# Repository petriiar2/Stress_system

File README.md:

# Physiological Monitoring System - Hardware Design & Sensor Integration

> **PCC1 Project | KTH Royal Institute of Technology | MSc Medical Engineering | Stockholm, 2026**  
> *This repository covers only the hardware design, sensor selection, wiring, and embedded firmware — the physical core of the system.*
> *Other aspects of the project ( software component , website ) not considered in this repository*

---

## Table of Contents

1. [Project Overview](#1-project-overview)
2. [System Architecture](#2-system-architecture)
3. [Internal Station — Patient Side](#3-internal-station--patient-side)
4. [External Station — Dentist Side](#4-external-station--dentist-side)
5. [Sensor Reference](#5-sensor-reference)
   - [Pressure Sensor](#51-pressure-sensor--abpdrrv060mgaa5)
   - [GSR Sensor](#52-gsr-sensor--galvanic-skin-response)
   - [Moisture Sensor](#53-moisture-sensor--adafruit-stemma)
   - [PPG Sensor](#54-ppg-sensor--max30102)
6. [Microcontrollers & Communication](#6-microcontrollers--communication)
7. [Power Supply](#7-power-supply)
8. [PCB](#8-pcb--enclosure)
9. [Current Limitations & Future Work](#9-current-limitations--future-work)
10. [Authorship & Contributions](#10-authorship--contributions)

---

## 1. Project Overview

Dental patients cannot speak during procedures. The traditional workaround — raising a hand to signal pain — forces dentists to split their attention between precise work under magnifying loupes and watching for a hand signal outside their field of view. It is also binary: the signal says *stop*, but conveys nothing about intensity or rising discomfort.

**BM-Dentist** is a Bluetooth-enabled physiological monitoring system that gives patients a richer, low-effort communication channel while providing dentists with objective, real-time data about patient comfort:

- A **squeeze ball** lets the patient signal pain by squeezing harder or with squeeze patterns (1 squeeze = mild, 2 = moderate, 3+ = severe).
- **Involuntary physiological sensors** (GSR + skin moisture) detect stress independently of the patient's conscious action — catching anxiety before it reaches the threshold of deliberate signalling.
- **LED ring indicators** on the dentist's side are positioned within their natural visual field and communicate pain and stress levels through colour and intensity without requiring the dentist to look away.
- A **web dashboard** logs all signals in real time and generates post-procedure statistics for quality improvement.

The system is designed as a prototype towards clinical use — not yet a certified medical device.

---

## 2. System Architecture

The system consists of three interconnected subsystems:

```
┌──────────────────────────────┐        BLE 5.0         ┌──────────────────────────────────────┐
│     INTERNAL STATION         │ ────────────────────►  │         EXTERNAL STATION             │
│        (Patient Side)        │                        │          (Dentist Side)              │
│                              │                        │                                      │
│  Pressure Sensor             │                        │  nRF52840 #1  ──UART──  nRF52840 #2  │
│  GSR Sensor                  │  XIAO nRF52840         │  LED Pain Ring          OLED Display │
│  Moisture Sensor             │  (BLE Peripheral)      │  LED Stress Ring        Buttons      │
│  MAX30102 (PPG)              │                        │  (BLE Central)          (BLE→USB)    │
│                              │                        │                                      │
└──────────────────────────────┘                        └──────────────┬───────────────────────┘
                                                                       │ USB Serial
                                                              ┌────────▼────────┐
                                                              │   WEB APP       │
                                                              │  (HTML/JS)      │
                                                              │  Real-time plot │
                                                              │  Post-proc stats│
                                                              └─────────────────┘
```

**Data flow summary:**

1. Sensors → Internal XIAO nRF52840 via analog ADC / I²C
2. Internal nRF → External nRF #1 via BLE UART (20 Hz)
3. External nRF #1 → LED rings (pain & stress visualisation) + External nRF #2 via UART
4. External nRF #2 → Computer via USB Serial → Web app

The web/software layer (dashboard, statistical analysis, CSV export) was developed by other team members and is referenced here for context only.

---

## 3. Internal Station — Patient Side

The internal station is the patient-held device. It houses all sensors, the microcontroller, and the BLE radio inside a custom 3D-printed enclosure designed for comfortable grip. Sensors that must contact the patient's skin (electrodes, moisture pad) exit the enclosure via JST connectors and are attached externally.

<p align="center">
  
  &nbsp;
  
</p>

### What it does

- Reads all four sensors at **20 Hz** via a continuous polling loop
- Packages readings into a CSV string: `pressure,gsr,moisture\n`
- Transmits over **BLE UART** to the external station
- Performs **min-max normalisation** against individually calibrated baseline values
- Drives a **status LED** (pin D10) to confirm active transmission

### Calibration

Before a procedure, a 5-second calibration sequence is triggered from the dentist side:

| Phase | Patient action | What is recorded |
|-------|---------------|-----------------|
| Resting | Hold balloon without squeezing | `P_min` — baseline pressure |
| Max squeeze | Squeeze as hard as possible | `P_max` — individual squeeze ceiling |
| Resting (continuous) | Stay relaxed | `GSR_baseline` — calm-state conductance average |

Subsequent readings are normalised as:

```
pressure_norm = (P_current - P_min) / (P_max - P_min)
stress_norm   = |GSR_current - GSR_baseline| / GSR_range
```

Patient gender and age category are also collected at calibration time (they affect pain thresholds), though in the current prototype the demographic adjustment coefficients are set to neutral (A=1.0, B=0.0) pending clinical data.

---

## 4. External Station — Dentist Side

The dentist-side station receives data wirelessly and translates it into immediate visual feedback — no screen-watching required.

<p align="center">
  
  &nbsp;
  
</p>

### Dual-microcontroller architecture

Two XIAO nRF52840 boards are connected by a UART link (TX/RX crossed: D6↔D7):

**nRF52840 #1 — Signal processing & LED control**

- Acts as **BLE Central**: scans for and connects to the internal station (`"SensorNode"`)
- Parses the incoming CSV string and normalises sensor values
- Maps normalised pain to the number of illuminated LEDs on the **green pain ring**
- Maps normalised stress to the number of illuminated LEDs on the **blue stress ring**
- Flips stress ring colour to **red** when stress normalised value > 75% (urgent alert)
- Supports two pain-signalling modes (selectable at runtime):
  - **Direct mode**: squeeze force → proportional LED count
  - **Pattern mode**: counts squeeze edges in a sliding time window → 1 squeeze = few LEDs, 2 = moderate, 3+ = many
- Forwards raw data to nRF #2 via UART during working mode

**nRF52840 #2 — Interface & data relay**

- Drives the **OLED menu display** and three navigation buttons (Up / Down / Enter)
- Sends configuration commands to nRF #1:
  - `CALIB,<gender>,<age>` — start calibration
  - `RESET_CALIB` — wipe calibration
  - `WORKCFG` — start working mode with selected options
  - `WORK_END` — stop working mode, return to sleep
- Relays raw sensor data to the computer via BLE → USB Serial

### Operating modes

| Mode | Description |
|------|-------------|
| **Sleep** | BLE connection active, command exchange only — no data streaming or LED updates |
| **Working** | Full data streaming at 20 Hz, LED feedback active, data sent to computer |

---

## 5. Sensor Reference

### 5.1 Pressure Sensor — ABPDRRV060MGAA5

| Property | Value |
|----------|-------|
| Type | Analog MEMS pressure sensor |
| Interface | Analog voltage → ADC pin D2 |
| Supply | 3.3 V |
| ADC resolution | 12-bit (0–4095) |
| Physical connection | Flexible tubing → squeeze balloon (water bottle) |
| Sampling rate | 20 Hz |

**Purpose:** The primary intentional pain-signalling channel. The patient squeezes a balloon; the pressure sensor sits inside the enclosure connected by tubing, so there is no direct electronic contact with the patient's hand. This improves hygiene and allows the balloon to be replaced/sterilised between patients.

**What we get:** An analogue voltage proportional to balloon pressure. After calibration, this maps linearly to a 0–100% pain scale. In pattern mode, rising edges are counted over a sliding window to detect discrete squeeze events.

**Why this sensor:** The specific sensor was supplied to the team and is well-matched to the use case — it captures a deliberate, high signal-to-noise signal that requires no inference to interpret.

---

### 5.2 GSR Sensor — Galvanic Skin Response

| Property | Value |
|----------|-------|
| Type | Skin conductance, analog |
| Interface | Analog voltage → ADC pin D0 |
| Supply | 3.3 V |
| Electrode placement | Index finger + middle finger |
| Sampling rate | 20 Hz |

**Purpose:** Continuous, involuntary stress monitoring. Galvanic skin response measures changes in sweat gland activity driven by the sympathetic nervous system. It captures anticipatory anxiety — the patient may start showing stress before consciously deciding to squeeze.

**What we get:** A slow-varying analogue voltage that rises as skin conductance increases (higher stress → more perspiration → lower resistance → higher conductance). The deviation from the calibrated calm baseline is used as the stress metric.

**Why this sensor:** GSR is a well-established proxy for sympathetic arousal. Practical alternatives (e.g., dedicated EDA modules) had longer delivery times; the chosen module was available immediately and is straightforward to integrate with a single ADC pin.

**Wiring:** Two finger-clip electrodes connect to the sensor module via wires that exit the enclosure through a JST socket. The module output goes to pin D0.

---

### 5.3 Moisture Sensor — Adafruit STEMMA

| Property | Value |
|----------|-------|
| Type | Capacitive soil moisture sensor (repurposed) |
| Interface | Analog voltage → ADC pin D1 |
| Supply | 3.3 V |
| Placement | Palm contact (external, JST connector) |
| Sampling rate | 20 Hz |

**Purpose:** Secondary stress indicator via perspiration. Stress-induced sweating changes the dielectric properties of the skin surface, which the capacitive sensor detects as a change in output voltage.

**What we get:** An analogue voltage that varies with surface moisture. In our pilot validation, moisture features showed near-complete binary separation between no-stress and stress conditions (AUC ≈ 0.02–0.035, Cliff's δ ≈ −0.93 to −0.96 — moisture *decreases* in our sensor's output with higher sweat, reflecting sensor polarity).

**Important caveat:** This sensor is designed for soil, not human skin. Its readings are highly sensitive to contact area and the rigid structure makes consistent placement difficult. It is treated as an **exploratory channel** in the current prototype. A future iteration should replace it with a skin-validated conductance or hydration sensor.

**Wiring:** The sensor pad exits the enclosure via JST connector and is held against the patient's palm.

---

### 5.4 PPG Sensor — MAX30102

| Property | Value |
|----------|-------|
| Type | Photoplethysmographic (optical heart rate + SpO₂) |
| Interface | I²C → pins D4 (SDA) / D5 (SCL) |
| Supply | 3.3 V |
| Interrupt pin | D3 (INT, optional) |

**Purpose:** Heart rate and pulse-related metrics are strong indicators of physiological stress. HRV (heart rate variability) in particular is sensitive to autonomic nervous system state.

**Current status:** ⚠️ **Not used in the current validated prototype.** One of the two purchased modules was defective (internal short). The second produced unstable readings. The JST connector and I²C lines remain present on the PCB for future integration. Results in this report do not rely on PPG data.

**Why this sensor:** Selected primarily on cost, feature set, and community support under a limited budget. A future iteration should source a verified module or use an alternative such as the MAX86150.

---

## 6. Microcontrollers & Communication

### Seeed Studio XIAO nRF52840

Used for all three microcontroller roles (internal station + both external boards).

| Spec | Value |
|------|-------|
| CPU | ARM Cortex-M4 @ 64 MHz |
| BLE | 5.0 integrated |
| ADC | 12-bit, 6 analog pins |
| Size | 20 × 17.5 mm |
| Supply | 3.3 V logic; powered via VBUS (5 V) |
| I²C | Hardware I²C on D4/D5 |
| UART | Hardware Serial1 on D6/D7 |

### BLE Configuration

- Internal board advertises as peripheral under name `"SensorNode"`
- External board #1 acts as central, scans and connects to `"SensorNode"`
- BLE UART service emulates serial over Bluetooth
- Data transmitted at 20 Hz; format: `"pressure,gsr,moisture\n"`
- ADC resolution set explicitly: `analogReadResolution(12)`

### UART Between External Boards

- Pins: `D6(#1) → D7(#2)`, `D7(#1) → D6(#2)` (TX/RX crossed)
- Baud rate: **115200**
- Commands flow #2 → #1; raw data flows #1 → #2
- In sleep mode: command exchange only. In working mode: full 20 Hz data stream.

---

## 7. Power Supply

### MB102 Breadboard Power Module

Used on both internal and external stations.

| Output | Used for |
|--------|----------|
| 5 V | XIAO VBUS pin, LED rings (5 V NeoPixel-type) |
| 3.3 V | All sensors (pressure, GSR, moisture, PPG) |

- Each XIAO board provides its own 3.3 V rail from its onboard regulator — two separate 3.3 V rails on the external station to distribute load.
- All boards and sensors share a **common ground**.
- MB102 includes overcharge/overdischarge protection.

---

## 8. PCB 

### PCB Design

Schematics and PCB layouts were designed in **KiCad**. Key design decisions:

- **JST connectors** used extensively throughout — sensors on the internal board and interface elements on the external board are all physically external to the PCB, so connectors allow clean cable management and easy swapping.
- PCB fabrication within university facilities was not feasible in the project timeline, so components were soldered onto **prototyping (perfboard) boards** following the KiCad layout.

KiCad project files are included in `/internal/` or `/external/` .

---

## 9. Current Limitations & Future Work

| Area | Current state | Planned improvement |
|------|--------------|---------------------|
| PPG (heart rate) | Unstable — excluded from prototype | Source verified MAX30102 or MAX86150; repeat validation |
| Moisture sensor | Exploratory — not skin-specific | Replace with validated skin conductance/hydration sensor |
| Demographic calibration | Coefficients set to neutral (A=1, B=0) | Add clinically derived thresholds per gender/age group |
| Clinical validation | Simulated stress (video induction), 1 subject | Ethically approved trials with real dental patients |
| Enclosure | Internal box only printed | Print external box; ergonomic redesign for sterile grip |
| Accessibility | Hand squeeze only | Add foot-operated or capacitive-touch alternative inputs |
| Sterilisation | Not yet validated | Material selection and sterilisation protocol testing |

---

## 10. Authorship & Contributions

The hardware design presented in this repository — including sensor selection and wiring,
PCB schematics, microcontroller configuration, BLE/UART communication
architecture, and embedded firmware for data acquisition and LED control — was designed
and implemented by **Iaroslav Petrishchev**.

The following parts of the system are the work of other team members and are therefore
not covered in this repository:

- **Web application & real-time dashboard** (HTML/JS, Chart.js, Web Serial API) — *Naya Nasr & Yanzi Yu*
- **Post-procedure statistical analysis & CSV export** — *Naya Nasr & Yanzi Yu*
- **Clinical research, sensor rationale & validation study** — *Naya Nasr & Yanzi Yu*

> Full project report available upon request.

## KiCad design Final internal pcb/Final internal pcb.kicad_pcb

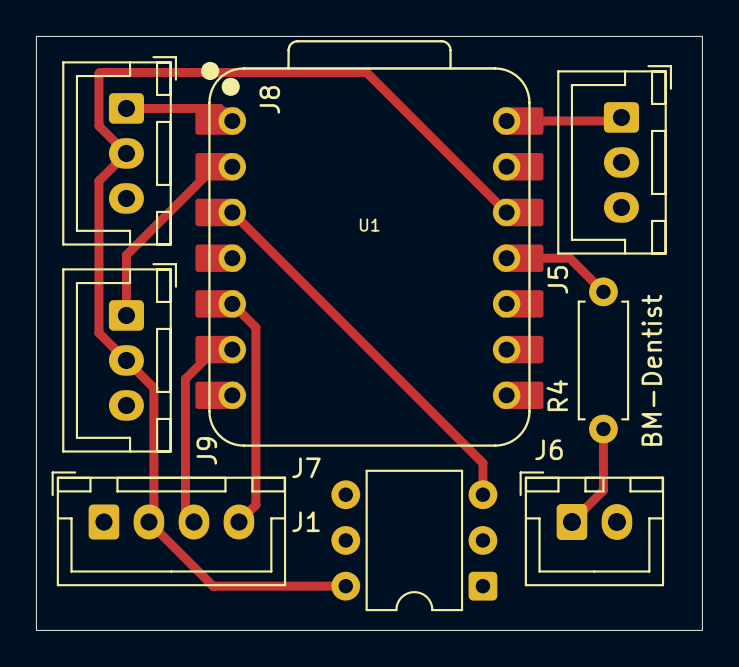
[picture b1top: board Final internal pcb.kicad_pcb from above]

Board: 2 copper layers, 37.0 x 33.0 mm, 8 parts (0 on the bottom side), 10 nets.

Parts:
J1: Conn_01x06; DIP-6_W7.62mm
J5, J8, J9: Conn_01x03_Socket; JST_XH_B3B-XH-A_1x03_P2.50mm_Vertical
J6: Conn_01x02_Socket; JST_XH_B2B-XH-A_1x02_P2.50mm_Vertical
J7: Conn_01x04_Socket; JST_XH_B4B-XH-A_1x04_P2.50mm_Vertical
R4: 220 R; R_Axial_DIN0207_L6.3mm_D2.5mm_P7.62mm_Horizontal
U1: XIAO-nRF52840-DIP

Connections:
3.3V: J1.6, J7.2, J8.2, J9.2, U1.12 (3V3)
5V: J5.1, U1.14 (VBUS)
GND: J1.1, J5.3, J6.2, J7.1, J8.3, J9.3, U1.13 (GND)
unnamed: J1.3, U1.3 (P0.28_AIN4_LOW_A2_D2)
unnamed: J6.1, R4.2
unnamed: J7.3, U1.6 (P0.05_AIN3_A5_D5)
unnamed: J7.4, U1.5 (P0.04_AIN2_A4_D4)
unnamed: J8.1, U1.1 (P0.02_AIN0_LOW_A0_D0)
unnamed: J9.1, U1.2 (P0.03_AIN1_LOW_A1_D1)
unnamed: R4.1, U1.11 (P1.15_MOSI_D10)

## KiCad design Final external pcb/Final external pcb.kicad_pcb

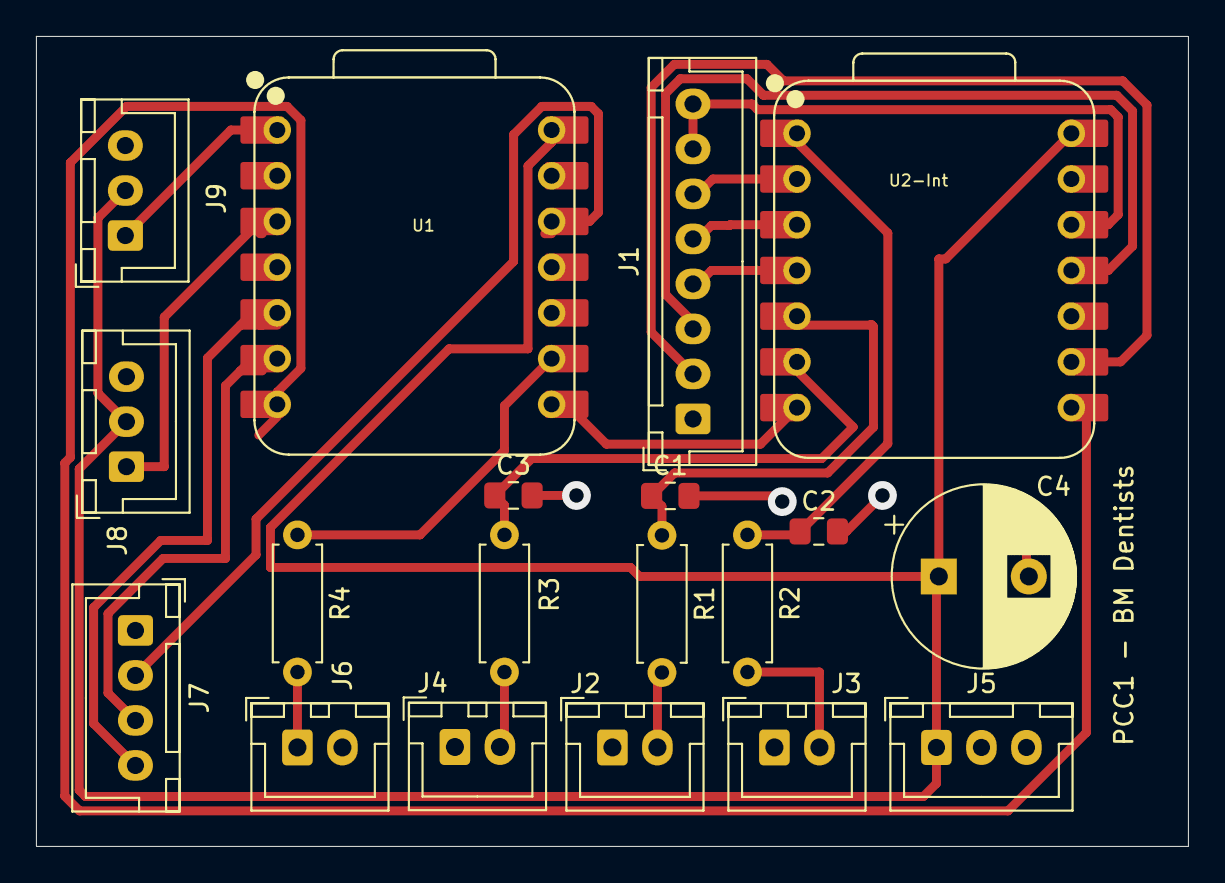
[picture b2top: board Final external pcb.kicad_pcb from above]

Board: 2 copper layers, 64.0 x 45.0 mm, 19 parts (0 on the bottom side), 23 nets.

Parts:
C1, C2, C3: 0.1 nF; C_0805_2012Metric_Pad1.18x1.45mm_HandSolder
C4: 1000uF; CP_Radial_D10.0mm_P5.00mm
J1: Conn_01x08_Socket; JST_XH_B8B-XH-A_1x08_P2.50mm_Vertical
J2, J3, J4, J6: Conn_01x02_Socket; JST_XH_B2B-XH-A_1x02_P2.50mm_Vertical
J5, J8, J9: Conn_01x03_Socket; JST_XH_B3B-XH-A_1x03_P2.50mm_Vertical
J7: Conn_01x04_Socket; JST_XH_B4B-XH-A_1x04_P2.50mm_Vertical
R1, R2, R3: 10k R; R_Axial_DIN0207_L6.3mm_D2.5mm_P7.62mm_Horizontal
R4: 220 R; R_Axial_DIN0207_L6.3mm_D2.5mm_P7.62mm_Horizontal
U1, U2-Int: XIAO-nRF52840-DIP

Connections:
3.3V_1: J7.2, U1.12 (3V3)
3.3V_2: J1.7, J1.8, U2-Int.12 (3V3)
5V: C4.1, J5.1, J8.2, J9.2, U1.14 (VBUS), U2-Int.14 (VBUS)
B1: C1.1, R1.1, U2-Int.5 (P0.04_AIN2_A4_D4)
B2: C2.1, R2.1, U2-Int.1 (P0.02_AIN0_LOW_A0_D0)
B3: C3.1, R3.1, U2-Int.6 (P0.05_AIN3_A5_D5)
GND: C1.2, C2.2, C3.2, C4.2, J1.1, J2.1, J3.1, J4.1, J5.3, J6.2, J7.1, J8.3, J9.3, U1.13 (GND), U2-Int.13 (GND)
unnamed: J1.2, U2-Int.9 (P1.13_SCK_D8)
unnamed: J1.3, U2-Int.11 (P1.15_MOSI_D10)
unnamed: J1.4, U2-Int.4 (P0.29_AIN5_LOW_A3_D3)
unnamed: J1.5, U2-Int.3 (P0.28_AIN4_LOW_A2_D2)
unnamed: J1.6, U2-Int.2 (P0.03_AIN1_LOW_A1_D1)
unnamed: J2.2, R1.2
unnamed: J3.2, R2.2
unnamed: J4.2, R3.2
unnamed: J6.1, R4.2
unnamed: J7.3, U1.6 (P0.05_AIN3_A5_D5)
unnamed: J7.4, U1.5 (P0.04_AIN2_A4_D4)
unnamed: J8.1, U1.3 (P0.28_AIN4_LOW_A2_D2)
unnamed: J9.1, U1.1 (P0.02_AIN0_LOW_A0_D0)
unnamed: U1.7 (P1.11_TX_D6), U2-Int.8 (P1.12_RX_D7)
unnamed: U1.8 (P1.12_RX_D7), U2-Int.7 (P1.11_TX_D6)
unnamed: R4.1, U1.9 (P1.13_SCK_D8)

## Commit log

2026-03-17 Fix formatting in system architecture diagram
2026-03-17 Revise README for clarity and project scope
    Updated project description and clarified repository focus.
2026-03-17 Revise PCB section and remove enclosure content
    Updated PCB section and removed enclosure details.
2026-03-17 Photos
2026-03-17 Revise README with updated web app and station details
    Updated diagrams and descriptions for internal and external stations.
2026-03-17 Improve image display in README.md
    Updated image formatting in README for better alignment.
2026-03-17 Update README with prototype images and descriptions
    Added images and updated descriptions for internal and external prototypes.
2026-03-17 Change image file extensions from PNG to JPEG
2026-03-17 Add authorship and contributions section to README
    Added authorship and contributions section detailing team members' roles.
2026-03-17 Add Authorship & Contributions section to README
2026-03-17 External_part files
